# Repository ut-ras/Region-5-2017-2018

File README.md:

# Region 5 2017-2018
## [Region 5 Robotics Competition](http://r5conferences.org/competitions/robotics-competition/)

### This year we are using the Arduino IDE to program our microcontrollers.
#### [install link](https://www.arduino.cc/en/Main/Software)
#### To set up your laptop:
#### 0. Install the Arduino IDE
#### 1. Clone the Repository
#### 2. Add all the libraries in the ./src/librares/ folder through the arduino IDE
### The lead of Software is Cole Thompson

# Region-5-2017-2018

## WE'RE GONNA <s>WIN</s> MEME THIS YEAR FOLKS

## YEAH WE ARE!!!

## Groups
Drive System</br>
Line Following and Intersection Detection</br>
Token Control and Storage</br>
Field Mapping, Data Logging, and Debugging </br>

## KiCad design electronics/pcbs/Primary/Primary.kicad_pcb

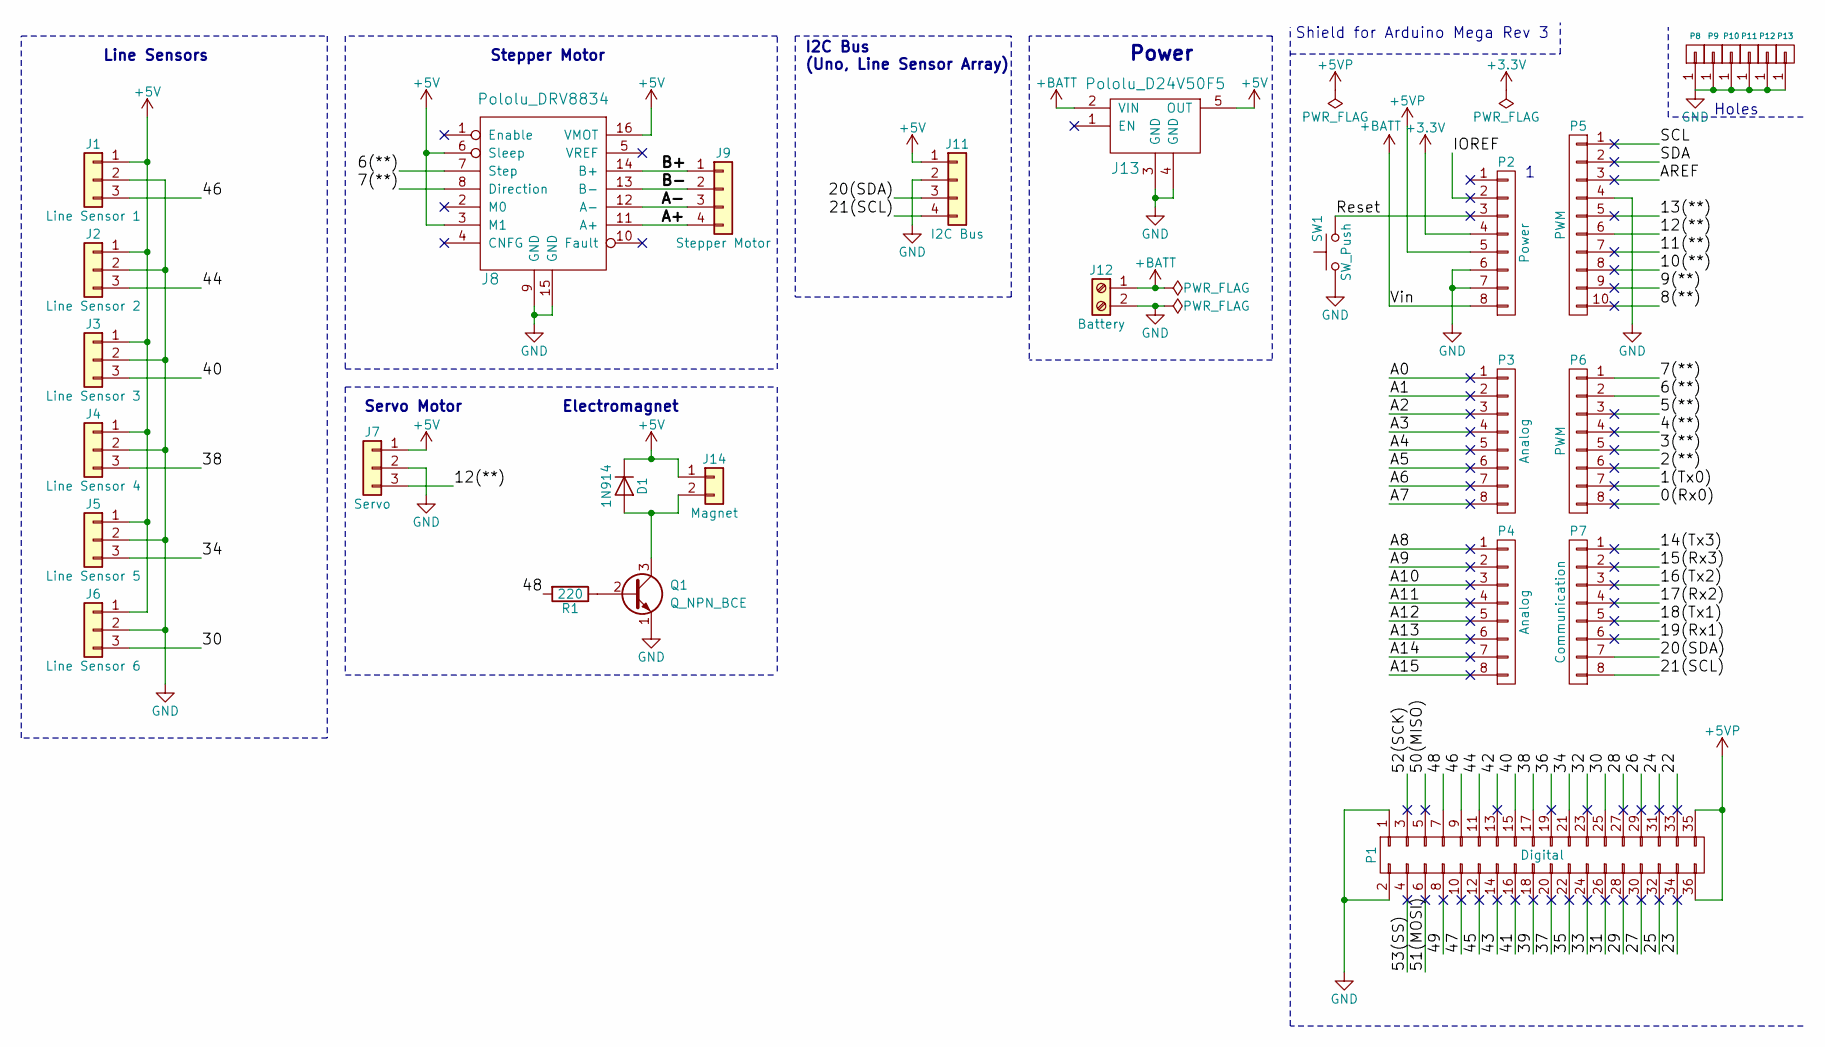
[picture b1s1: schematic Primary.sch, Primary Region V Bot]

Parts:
D1: 1N914; D_DO-15_P5.08mm_Vertical_KathodeUp
J1: Line Sensor 1; SL-103-X-XX_1x03
J2: Line Sensor 2; SL-103-X-XX_1x03
J3: Line Sensor 3; SL-103-X-XX_1x03
J4: Line Sensor 4; SL-103-X-XX_1x03
J5: Line Sensor 5; SL-103-X-XX_1x03
J6: Line Sensor 6; SL-103-X-XX_1x03
J7: Servo; SL-103-X-XX_1x03
J8: Pololu_DRV8834
J9: Stepper Motor; SL-104-X-XX_1x04
J11: I2C Bus; SL-104-X-XX_1x04
J12: Battery; TerminalBlock_bornier-2_P5.08mm
J13: Pololu_D24V50F5
J14: Magnet; SL-102-X-XX_1x02
P1: Digital; Socket_Strip_Arduino_2x18
P2: Power; Socket_Strip_Arduino_1x08
P3, P4: Analog; Socket_Strip_Arduino_1x08
P5: PWM; Socket_Strip_Arduino_1x10
P6: PWM; Socket_Strip_Arduino_1x08
P7: Communication; Socket_Strip_Arduino_1x08
P8, P9, P10, P11, P12, P13: CONN_01X01; Arduino_1pin
Q1: Q_NPN_BCE; TO-18-3
R1: 220; R_Axial_DIN0309_L9.0mm_D3.2mm_P5.08mm_Vertical
SW1: SW_Push; SW_PUSH_6mm_h4.3mm

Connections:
+3V3: P2.4
+5V: D1.1 (K), J1.1, J2.1, J3.1, J4.1, J5.1, J6.1, J7.1, J8.3 (M1), J8.6 (Sleep), J8.16 (VMOT), J11.1, J13.5 (OUT), J14.1
+5VP: P1.35, P1.36, P2.5
+BATT: J12.1, J13.2 (VIN), P2.8
/0(Rx0): P6.8
/1(Tx0): P6.7
/2(**): P6.6
/3(**): P6.5
/4(**): P6.4
/5(**): P6.3
/6(**): J8.7 (Step), P6.2
/7(**): J8.8 (Direction), P6.1
/8(**): P5.10
/9(**): P5.9
/10(**): P5.8
/11(**): P5.7
/12(**): J7.3, P5.6
/13(**): P5.5
/14(Tx3): P7.1
/15(Rx3): P7.2
/16(Tx2): P7.3
/17(Rx2): P7.4
/18(Tx1): P7.5
/19(Rx1): P7.6
/20(SDA): J11.3, P7.7
/21(SCL): J11.4, P7.8
/22: P1.33
/23: P1.34
/24: P1.31
/25: P1.32
/26: P1.29
/27: P1.30
/28: P1.27
/29: P1.28
/30: J6.3, P1.25
/31: P1.26
/32: P1.23
/33: P1.24
/34: J5.3, P1.21
/35: P1.22
/36: P1.19
/37: P1.20
/38: J4.3, P1.17
/39: P1.18
/40: J3.3, P1.15
/41: P1.16
/42: P1.13
/43: P1.14
/44: J2.3, P1.11
/45: P1.12
/46: J1.3, P1.9
/47: P1.10
/48: P1.7, R1.2
/49: P1.8
/50(MISO): P1.5
/51(MOSI): P1.6
/52(SCK): P1.3
/53(SS): P1.4
/A0: P3.1
/A1: P3.2
/A2: P3.3
/A3: P3.4
/A4: P3.5
/A5: P3.6
/A6: P3.7
/A7: P3.8
/A8: P4.1
/A9: P4.2
/A10: P4.3
/A11: P4.4
/A12: P4.5
/A13: P4.6
/A14: P4.7
/A15: P4.8
/A+: J8.11 (A+), J9.4
/A-: J8.12 (A-), J9.3
/AREF: P5.3
/B+: J8.14 (B+), J9.1
/B-: J8.13 (B-), J9.2
/IOREF: P2.2
/Reset: P2.3, SW1.2
/SCL: P5.1
/SDA: P5.2
GND: J1.2, J2.2, J3.2, J4.2, J5.2, J6.2, J7.2, J8.9 (GND), J8.15 (GND), J11.2, J12.2, J13.3 (GND), J13.4 (GND), P1.1, P1.2, P2.6, P2.7, P5.4, P8.1, P9.1, P10.1, P11.1, P12.1, P13.1, Q1.1 (E), SW1.1
unnamed: D1.2 (A), J14.2, Q1.3 (C)
unnamed: Q1.2 (B), R1.1

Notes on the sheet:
Shield for Arduino Mega Rev 3
Holes
Line Sensors
Stepper Motor
I2C Bus (Uno, Line Sensor Array)
Servo Motor
Power
Electromagnet

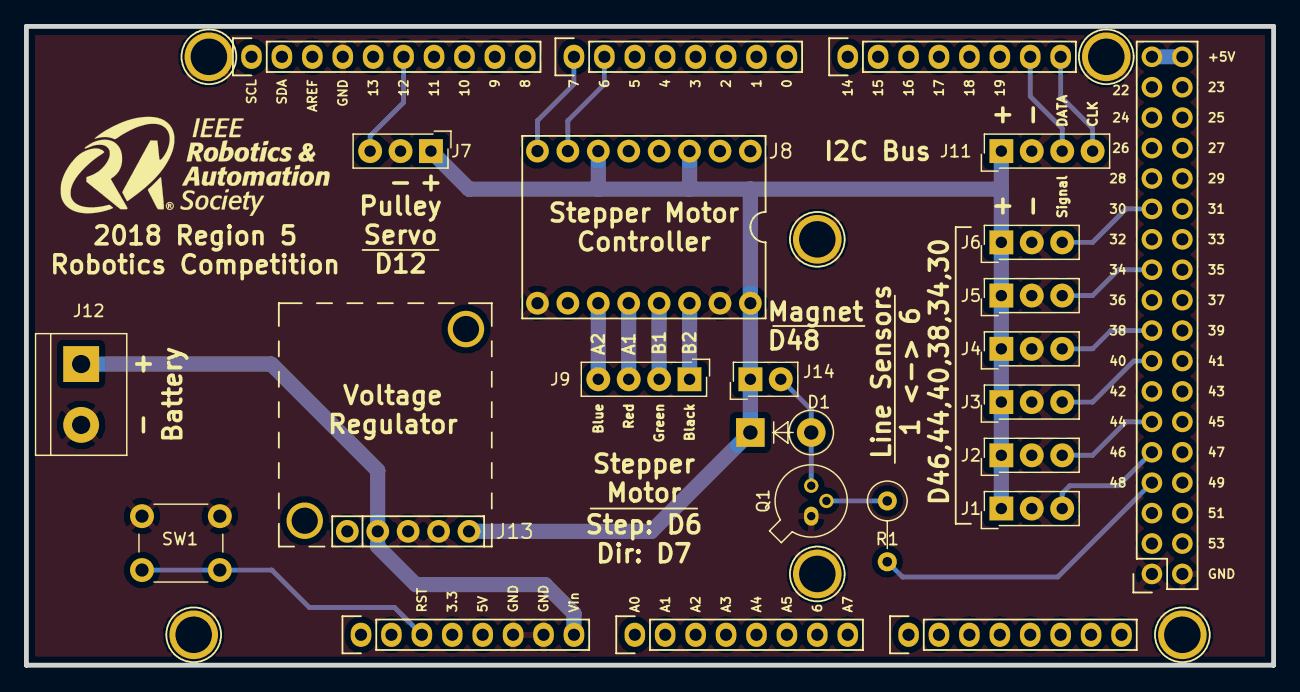
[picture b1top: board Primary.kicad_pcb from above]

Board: 2 copper layers, 104.1 x 53.3 mm, 30 parts (0 on the bottom side), 23 nets.

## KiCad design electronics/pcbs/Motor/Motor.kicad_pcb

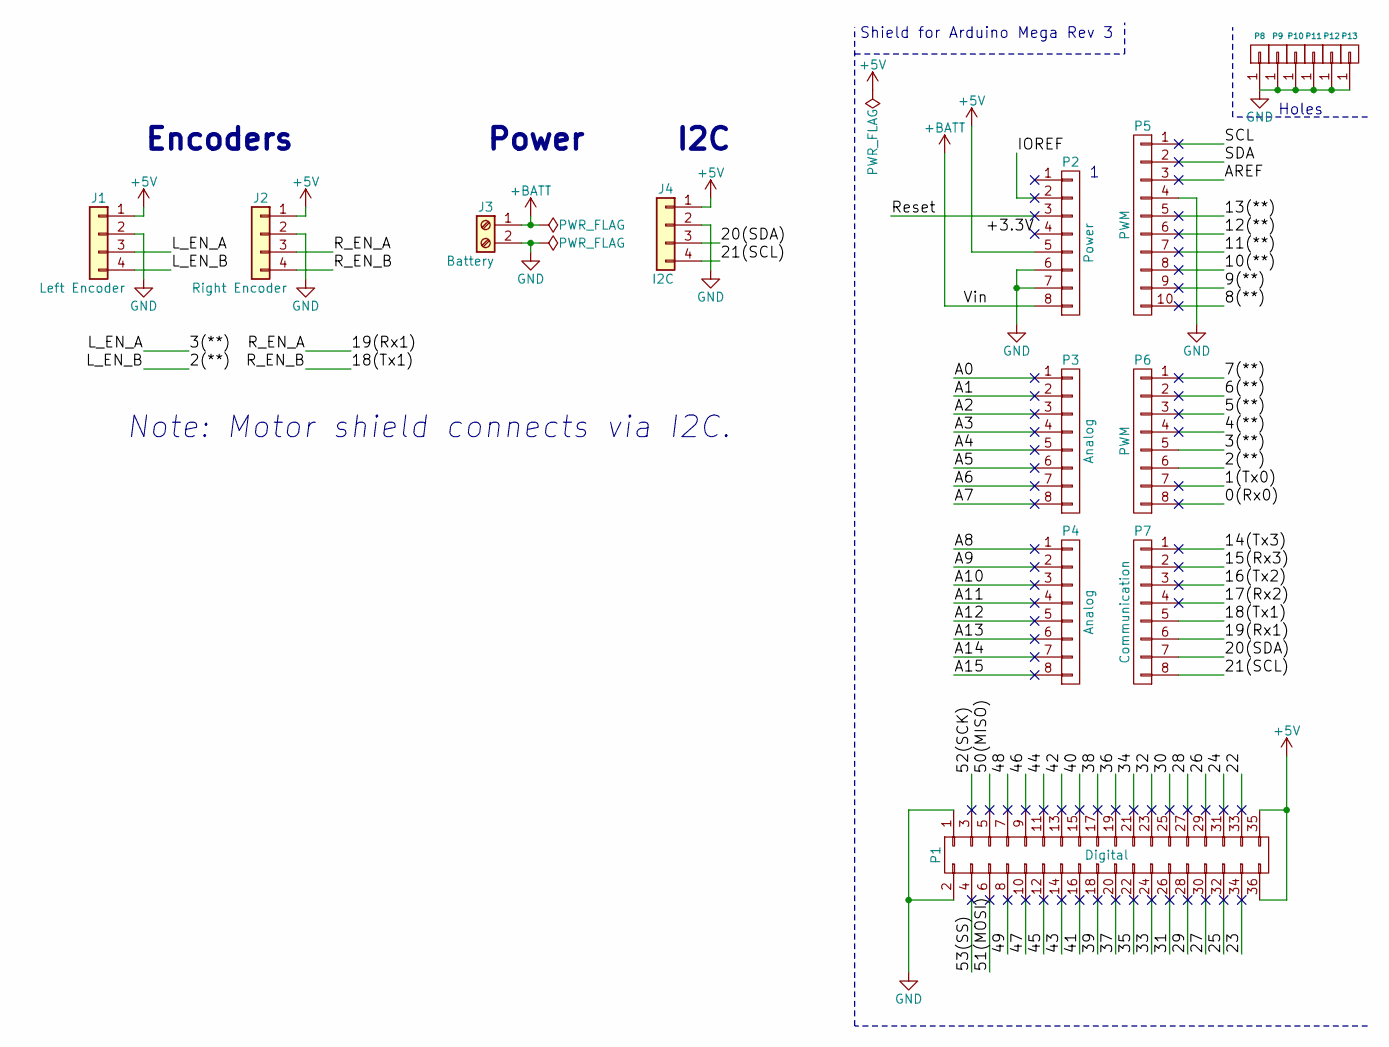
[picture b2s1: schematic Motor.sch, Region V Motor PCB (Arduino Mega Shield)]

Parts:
J1: Left Encoder; SL-104-X-XX_1x04
J2: Right Encoder; SL-104-X-XX_1x04
J3: Battery; TerminalBlock_bornier-2_P5.08mm
J4: I2C; SL-104-X-XX_1x04
P1: Digital; Socket_Strip_Arduino_2x18
P2: Power; Socket_Strip_Arduino_1x08
P3, P4: Analog; Socket_Strip_Arduino_1x08
P5: PWM; Socket_Strip_Arduino_1x10
P6: PWM; Socket_Strip_Arduino_1x08
P7: Communication; Socket_Strip_Arduino_1x08
P8, P9, P10, P11, P12, P13: CONN_01X01; Arduino_1pin

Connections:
+5V: J1.1, J2.1, J4.1, P1.35, P1.36, P2.5
+BATT: J3.1, P2.8
/0(Rx0): P6.8
/1(Tx0): P6.7
/2(**): J1.4, P6.6
/3(**): J1.3, P6.5
/4(**): P6.4
/5(**): P6.3
/6(**): P6.2
/7(**): P6.1
/8(**): P5.10
/9(**): P5.9
/10(**): P5.8
/11(**): P5.7
/12(**): P5.6
/13(**): P5.5
/14(Tx3): P7.1
/15(Rx3): P7.2
/16(Tx2): P7.3
/17(Rx2): P7.4
/18(Tx1): J2.4, P7.5
/19(Rx1): J2.3, P7.6
/20(SDA): J4.3, P7.7
/21(SCL): J4.4, P7.8
/22: P1.33
/23: P1.34
/24: P1.31
/25: P1.32
/26: P1.29
/27: P1.30
/28: P1.27
/29: P1.28
/30: P1.25
/31: P1.26
/32: P1.23
/33: P1.24
/34: P1.21
/35: P1.22
/36: P1.19
/37: P1.20
/38: P1.17
/39: P1.18
/40: P1.15
/41: P1.16
/42: P1.13
/43: P1.14
/44: P1.11
/45: P1.12
/46: P1.9
/47: P1.10
/48: P1.7
/49: P1.8
/50(MISO): P1.5
/51(MOSI): P1.6
/52(SCK): P1.3
/53(SS): P1.4
/+3.3V: P2.4
/A0: P3.1
/A1: P3.2
/A2: P3.3
/A3: P3.4
/A4: P3.5
/A5: P3.6
/A6: P3.7
/A7: P3.8
/A8: P4.1
/A9: P4.2
/A10: P4.3
/A11: P4.4
/A12: P4.5
/A13: P4.6
/A14: P4.7
/A15: P4.8
/AREF: P5.3
/IOREF: P2.2
/Reset: P2.3
/SCL: P5.1
/SDA: P5.2
GND: J1.2, J2.2, J3.2, J4.2, P1.1, P1.2, P2.6, P2.7, P5.4, P8.1, P9.1, P10.1, P11.1, P12.1, P13.1

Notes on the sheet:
Shield for Arduino Mega Rev 3
Holes
Encoders
Power
I2C
Note: Motor shield connects via I2C.

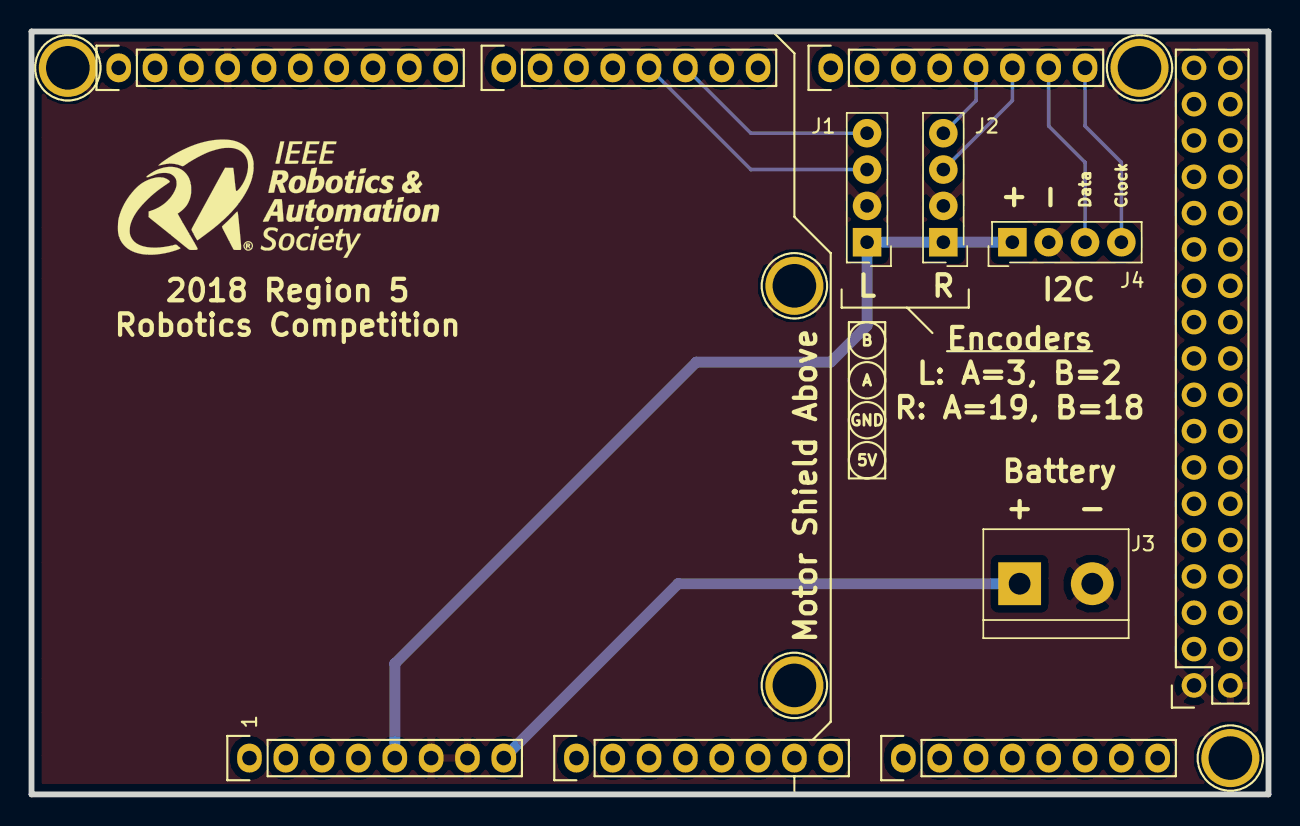
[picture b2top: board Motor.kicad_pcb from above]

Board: 2 copper layers, 86.5 x 53.3 mm, 16 parts (0 on the bottom side), 9 nets.

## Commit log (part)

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2017-11-05 started tokenControl.h
2017-11-06 updated tokenControl header
2017-11-06 added main file
2017-11-06 fleshing out the graph init
2017-11-09 finished this fugly map initialization
2017-11-09 started test folder
2017-11-12 Updated motor drivers
2017-11-12 added deposit in tokenControl
2017-11-13 implemented node.h and node.cpp
2017-11-13 added current Node to graph
2017-11-16 working on intersections and map
2017-11-19 added Log class
2017-11-20 Made the encoder class, changed up the motorController class, and need to make the encoderReceiver class and connect everything
2017-11-20 node toString for log
2017-11-20 Started Log File code
    -Use EEPROM to write to log files
    -Added a header sequence to look for in EEPROM
    -Edited .h file to have more helper functions
2017-11-30 implements toString() for Node and Graph and thereby establishes formatting conventions for transmission to GUI debugger
2017-12-03 added setters for current direction/node
2017-12-03 updated graph init
2017-12-03 node typeo
2017-12-03 testGraph stuff
2017-12-04 added graph function
2017-12-04 I added some MotorControl commands
2017-12-04 implemented getNode
2017-12-07 Added TokenControl.cpp and associated files
2017-12-07 Deposit tokens in box
    Function for picking up token from the funnel and then dropping it onto
    the field
2017-12-07 Addeed comments and clarification to tokenControl
2017-12-07 intersection stuff
2017-12-07 moved mid-level to drivers
2017-12-07 Node.toString now uses lookup tables and we consider intersections on the grey box as nodes
2017-12-10 folder changes
2017-12-10 include statements
2017-12-10 Removed CLion Stuff
2017-12-10 motor test file
2017-12-10 Fixed the constructor for motorController
2017-12-11 Made a file about which cpp gets flashed to which board
2018-01-23 added cpp files for magnet, servo, stepper
2018-01-23 Fixed Government shutdown
2018-01-23 comment out Hashmp.h and include my exact loc for hashmap
2018-01-23 graph test
2018-01-23 servo kinda works
2018-01-23 leggooooo
2018-01-26 finished servo implementation
2018-01-26 started magnet
2018-01-30 another attempt
2018-01-30 Modified Structure of TokenControl.cpp
    Increased abstraction by grouping pickup into one function
2018-01-30 fixed some errros in node.h
2018-01-30 fixed the B to Bl constants
2018-01-30 fix some more compile errors
2018-02-02 updated code
2018-02-02 adjusted direction
2018-02-02 Finished Debugging
2018-02-02 Finished Code
2018-02-06 added hash test
2018-02-06 Arduino IDE doesnt like folders
2018-02-06 Removed all file dependencies
    After nuking all the files, I removed all the local dependencies so code compiles.
2018-02-06 Removed some extra files
2018-02-09 src is the magic word
2018-02-09 debug team changed string to const char*
2018-02-09 Stepper Motor Driver Library
2018-02-09 changed the Graph constructor
2018-02-09 fixed header and cpp method names
2018-02-09 kill me pls
2018-02-13 Editted tokenControl.cpp to match new servo.cpp
    Used degrees instead of distances.
2018-02-13 adjusted servo test
2018-02-13 Removed extra libraries I added:
2018-02-16 want to checkout
2018-02-16 Started on disk rotation (not sure what the previous code did)
2018-02-19 compile errors
2018-02-20 debugging
2018-02-20 final h file
2018-02-20 fine tuning
2018-02-23 debugging, were using too much mem
2018-02-27 bug is in Node* adj2[37][8] in graph.cpp
2018-03-02 Wrote stepper driver.
2018-03-02 graph printing correctly
2018-03-06 modified graph test for use with GUI
2018-03-06 fixed some bugs?
2018-03-08 Edited README
    Added essential information to the README
2018-03-09 graph init working on uno
2018-03-19 cleaned up graph stuff
2018-03-19 moved map into src
2018-03-20 Intesection Sensor Works
    1. Changed wiring to get the side line sensors working
    2. Made sure each individual line sensor works
    3. Getting Raw Data from the sensors
2018-03-20 begin implementing the intersection tests
2018-03-20 put visuals for the intersetion tests in the notes folder
2018-03-20 finalizes implementation of the 4 tests outlined in the ppt in notes. Will likely contain bugs and need further testing and tweaking
2018-03-21 missing some adj list entries
2018-03-21 cleaned up tests, working
2018-03-21 Primary PCB: Added first draft of schematic and PCB.
2018-03-21 Primary PCB: Removed one of the I2C bus sockets - we'll only need one.
2018-03-21 Primary PCB: Added pinout labels and pin labels to silkscreen.
2018-03-21 Motor PCB: Created a footprint for the Arduino Nano. Assigned footprints to the components on the Motor schematic.
2018-03-21 Primary PCB: Regulator screw holes are now plated and connected to GND. Also hid the PX labels for the Arduino headers.
2018-03-21 Primary PCB: Power the Arduino with VBATT rather than Regulated 5V.
2018-03-21 Motor PCB: Added silkscreen label for battery and its polarity. Hid PX and UX labels for Arduino headers.
2018-03-22 Motor PCB: Starting over with the board, since we might switch to a Mega.
2018-03-22 Motor PCB: Created Mega template project.
2018-03-22 Motor PCB: Redesigned PCB. Swapped pins for Encoder R's A and B so that layout was easier.
2018-03-22 Primary/Motor PCBs: Rearranged the GND pin on breakout headers so that we can avoid needing two layers. This change makes the boards more easily prototyped using hobbyist tools like the OtherMill, wh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
2018-03-23 reorganization
2018-03-23 Added uno and nano files
    Still need to make the motorcontroller class for the uno file
2018-03-23 changed rgbsensor file
2018-03-23 testing stuff for TokenControl
2018-03-23 more fixes to token
2018-03-23 RGB sensor works
    Got RGB sensor to work. Need to improve on the thresholding of the colors. Chad will handle that
2018-03-23 encoder class
2018-03-23 git issues
2018-03-23 MotorControll cpp and H update
2018-03-23 Added GUI
2018-03-23 Updated Drive.ino file
2018-03-23 updated RGB comparisons
2018-03-23 cleanup
2018-03-23 syntax errors
2018-03-23 added dwf library
2018-03-24 Interrupt pin requirement added
2018-03-24 i love darth plagueis, but...
2018-03-25 updated R5MegaDrive
2018-03-26 Primary/Motor PCBs: Added logo and competition to board silkscreens.
2018-03-27 Adds new basic movement test
2018-03-27 Added Get Weighted Value function
    Added a function to get the weighted value of the line array
2018-03-27 updates the motor control and move test
2018-03-27 added line sensor code
    we're trying this out using thresholding. Max value is 4. need to test
2018-03-27 movement test
2018-03-27 encoder upate function testing
2018-03-27 time vars as doubles
2018-03-27 PID/encoder work but we need better kp ki kd
2018-03-27 velocity averaging test
2018-03-28 fixed one bug, testing some other things
2018-03-28 debug
2018-03-28 Changed PID Values
    Removed a way to stop the changing P Value
2018-03-29 auto tune test
2018-03-29 working PID's
2018-03-29 Added Tuning Sweep for PID Constants
    PI values have methods that can be swept over. I wrote a python script to read the output via serial, but we can also just look at the raw serial values which we will do.
2018-03-30 PID tuning helper functions
2018-03-30 drive - combined tests into main
2018-03-30 moving zip libs to archive
2018-03-30 missed one
2018-03-30 map access everywhere
2018-03-30 Updated Token Control Angles and Base for colour sensor
2018-03-30 func headers for turn thingy
2018-03-30 added more stuff for tokenControl...
2018-03-30 Made setMotorMode a lot shorter
2018-03-30 Fixed dumb syntax issues with tokenControl.cpp
2018-03-30 Implemented tick-wise turn functions
2018-03-30 Fixed compile issue with tokencontrol
2018-03-30 added tests and more compiling...
2018-03-30 updates the round1 function to reflect new syntax... incomplete
2018-03-30 Addition of turns to set mode for motors and fix for turn direction
2018-03-30 drive control updates
2018-03-30 syntax error
2018-03-30 more test stuffffffffff
2018-03-31 removed an incorrect change
2018-03-31 tonight's tests
2018-03-31 Primary PCB: Modified Primary to be more easily printed with labels on the OtherMill.
2018-03-31 Motor PCB: Modified PCB to be more easily printed with labels on the OtherMill.
2018-03-31 Primary PCB: Modified electromagnet circuit to power the magnet with a transistor.
2018-03-31 Motor PCB: Corrected PCB Previews
2018-03-31 Primary PCB: Corrected transistor pinout and footprint. Gave a value to the resistor attached to the transistor.
2018-04-01 tonights tests
2018-04-01 Deprecated the Autotune P Value
2018-04-01 Added I2C tests
    Added I2C tests. Next we need to actually make sure the commands are the correct commands and then make sure nothing is shorting in the hardware
2018-04-02 Implemented token counter in TokenControl and Graph
    Added getters and setters to Graph as well as calling graph functions
    from TokenControl
2018-04-02 fwd to intersection works, need to calib pointline
2018-04-02 extracts common segments into functions for more readable and flexible code. New functions allow us to write strategy in point-to-point fashion
2018-04-02 worked on round 2
2018-04-02 fixed misspelled comment, cuz I can
2018-04-02 altered the round2 path slightly to save time and added parameters and functions to address the changes in level (which of the 4 squares we are in)
2018-04-03 Minor fixes to GUI
2018-04-03 ready for intersection calibration
2018-04-03 commented temporarily for compile
2018-04-03 GUI improved
2018-04-03 0ing index array and other token stuff
2018-04-03 Removed pullup from pointline driver
2018-04-03 Changed the diff and added removed pull up resistors
    Changed the diff to 1000
    Removed pull up resistors
2018-04-04 serial input
2018-04-04 removed old line sensor stuff
2018-04-04 Finished recursion. Todo: token tracking API, node coordinate API
2018-04-04 Changed the values to the correct drive values
2018-04-04 Added Use array for array on the back
    Added the Use Array so the robot can move without linearray sensors before moving
2018-04-04 print tests
2018-04-04 added hardcode to nextintersection
2018-04-04 intersection bug
2018-04-04 Merge
2018-04-04 easy timing with intersection stuff
2018-04-04 Recalibrated distances and angles
2018-04-04 forgot to update constant in MotorControl
2018-04-04 added todo
2018-04-05 line sensor corrections
2018-04-05 random shit
2018-04-05 Pins for front arrayline fixed
2018-04-05 didnt mean to remove that
2018-04-05 memcpy
2018-04-05 memocpy fix
2018-04-05 adjustments
2018-04-05 intersection detection #3
2018-04-05 I hate Token Control
2018-04-05 Working line follow and intersections???
2018-04-05 forgot these ^
2018-04-05 added simple offset-based line centering function
2018-04-06 organization
2018-04-06 added a func to test
2018-04-06 Revert "Merge branch 'master' of https://github.com/ut-ras/Region-5-2017-2018"
    This reverts commit 037a0fbc4ae76f4c46d67a12c0cc19c0276b78da, reversing
    changes made to b6dbf6b5768469ba93bd185f8e141920d5343d16.
2018-04-06 correct dc motor overshoot on stop
2018-04-06 comments
2018-04-06 print overshoot
2018-04-06 Changed value to make code compile
2018-04-06 forgot a merge thing
2018-04-06 Added turn and backwards code
2018-04-06 Token Control, please never make me commit again
    Note: I moved a function from intersection array to public and created a
    declaration in driveControl.h cause code wasn't compiling
2018-04-06 Magenta more lenient
2018-04-07 removed counting code
2018-04-07 smoother speed
2018-04-07 cutoff
2018-04-07 increase lowest speed
2018-04-07 temporarily disabled
2018-04-07 trying without back sensor
2018-04-07 MegaMain: Added start/stop button code
    Added functions to wait for start button and check for stop button.
    Initialized pins 2 and 3 as INPUT_PULLUP for start and stop buttons respectively.
2018-04-07 add function to return pointline data for the boxes
2018-04-07 Added polling stop button to Drive and changed stop button in Main to interrupt
2018-04-07 retrieve all my old functions
2018-04-07 Commented out changes
2018-04-07 cmds
2018-04-07 changed motor ports
2018-04-07 Changed the motor directions
2018-04-07 Return to white compiles and works
2018-04-07 more driveControl commenting stuff
2018-04-07 just turn
2018-04-07 encoder tick logic
2018-04-07 stop
2018-04-07 try this
2018-04-07 print
2018-04-07 figured out turning
2018-04-07 Changed motor code
2018-04-07 token test
2018-04-07 updating my Main shyte
2018-04-07 Added buttons
2018-04-07 more stuff
2018-04-07 aaah
2018-04-07 aaaaaah
2018-04-07 testGUI and testSimple functions created
2018-04-07 pin defs
2018-04-07 main mega removing buttons
2018-04-07 added func for grey box
2018-04-07 quick and dirty round 3 algorithm called 'allIn( )
